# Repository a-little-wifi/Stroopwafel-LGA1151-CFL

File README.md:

# Stroopwafel LGA1151 Intel Coffee Lake motherboard

Trying to see how far I can get with implementing a modern-ish Intel platform in KiCad using public documentation and leaked schematics.

Here's some work in progress pictures (random layout (or ATX standard successor??? 👀)):

Inspired by LCSC carrying LGA1151 sockets: https://www.lcsc.com/product-detail/C2761532.html (thanks for the footprint)

Thanks @mothenjoyer69 for extracting the PCH footprint from a random laptop boardview (LA-F711P)

CPU and PCH schematic symbols fully copied (and partially corrected) from pdf schematics by hand (took like 3 days...)

It's called Stroopwafel because I was eating a stroopwafel when I was trying to come up with a name. Also stroopwafels are supposed to go with coffee and it's Coffee Lake... get it?....

Mostly using LCFC NM-B551 (Lenovo Tiny5) and Wistron 17557-1 Copperbox (Acer N4660G my beloved) schematics for reference atm

The PCH footprint and symbol in this project should be applicable to (most of) Intel's 300 and 400 series chipsets. 300 series goes with 8th/9th gen and 400 series goes with 10th/11th gen.  
I'll be using a 300-series chipset for this project (probably Z390), since I'm using LGA1151. For 400 series you need LGA1200.

The goal is to create an easy to understand board and schematic layout that breaks out as much of the platform capabilities as possible.

Might build a laptop with a desktop CPU for fun later.

Am I insane? maybe. But I don't really see why I shouldn't try at the moment. It's a fun experiment at least.

No idea what board layout I'll use yet, but I don't feel like using a standard ATX formfactor, there's already plenty of boards like that. I kinda wanna make the PCH and CPU sections modular but I'll have to see about the practicalities of that.

I don't know how I'm gonna handle the EC and firmware yet, probably just gonna yoink it from an existing board and pray that it works without too much modification. I'm open to help regarding this. Maybe coreboot/libreboot?

Routing DDR4 will be fun.

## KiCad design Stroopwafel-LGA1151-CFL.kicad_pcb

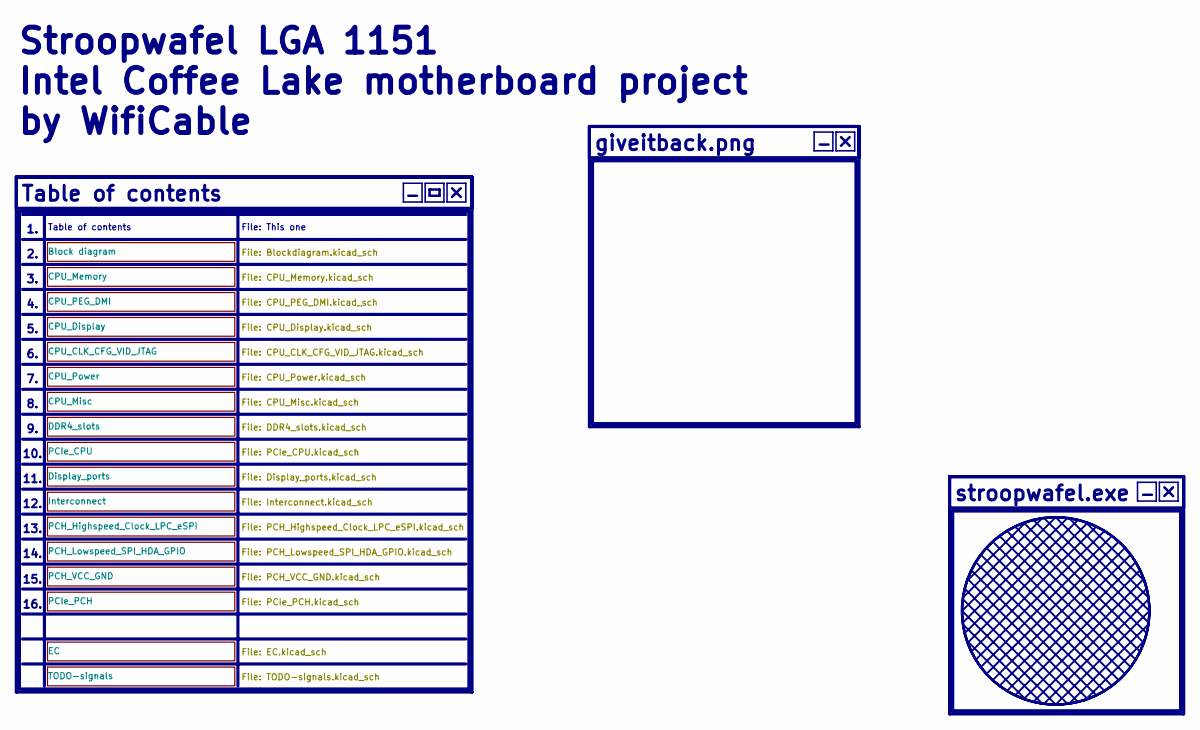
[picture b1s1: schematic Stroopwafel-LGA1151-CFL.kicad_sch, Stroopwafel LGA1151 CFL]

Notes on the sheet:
Stroopwafel LGA 1151 Intel Coffee Lake motherboard project by WifiCable
Table of contents
stroopwafel.exe
11.
15.
File: This one
giveitback.png
14.
16.
13.
10.
12.

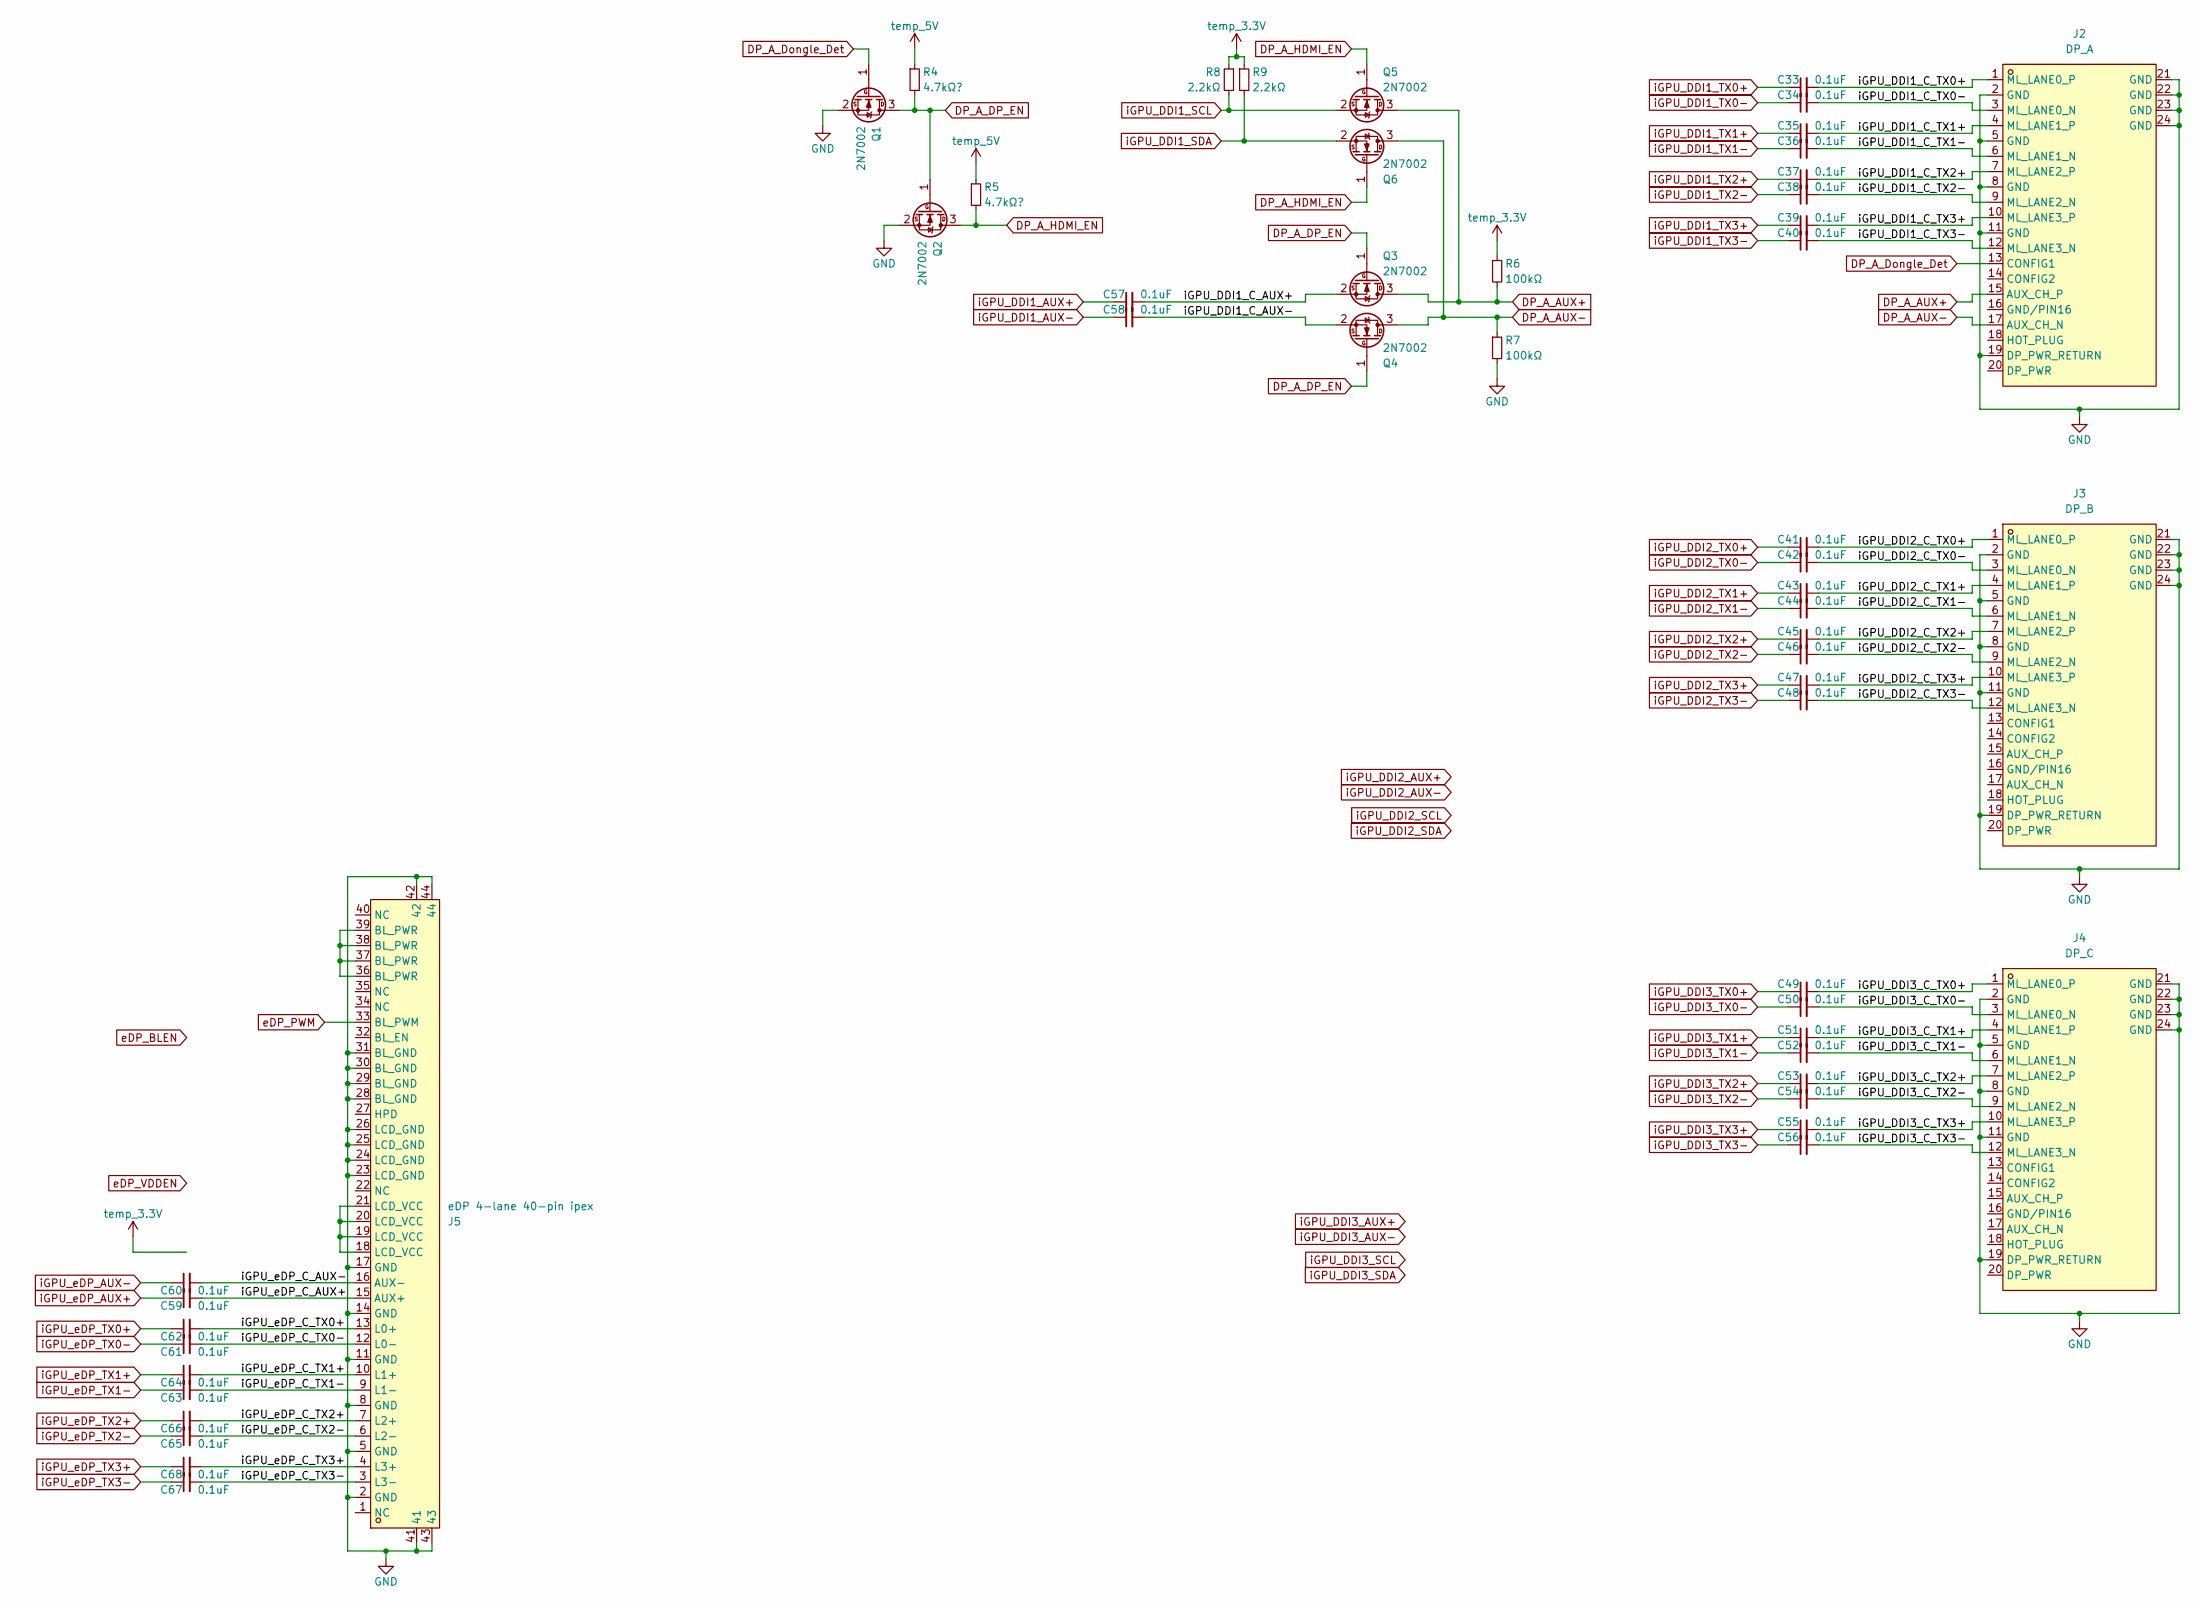
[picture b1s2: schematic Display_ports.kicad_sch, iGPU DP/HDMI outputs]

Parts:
C33, C34, C35, C36, C37, C38, C39, C40, C41, C42, C43, C44, C45, C46, C47, C48, C49, C50, C51, C52, C53, C54, C55, C56, C57, C58, C59, C60, C61, C62, C63, C64, C65, C66, C67, C68: 0.1uF; C_0402_1005Metric
J2: DP_A; DP-SMD_HYC16-DP20-178; LCSC Part C711350
J3: DP_B; DP-SMD_HYC16-DP20-178; LCSC Part C711350
J4: DP_C; DP-SMD_HYC16-DP20-178; LCSC Part C711350
J5: eDP 4-lane 40-pin ipex; 40pIPEX_20455-040E-76
Q1, Q2, Q3, Q4, Q5, Q6: 2N7002; SOT-23
R4, R5: 4.7kΩ?; R_0402_1005Metric
R6, R7: 100kΩ; R_0402_1005Metric
R8, R9: 2.2kΩ; R_0402_1005Metric

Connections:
/Display_ports/iGPU_DDI1_C_AUX+: C57.2, Q3.2 (S)
/Display_ports/iGPU_DDI1_C_AUX-: C58.2, Q4.2 (S)
/Display_ports/iGPU_DDI1_C_TX0+: C33.2, J2.1 (ML_LANE0_P)
/Display_ports/iGPU_DDI1_C_TX0-: C34.2, J2.3 (ML_LANE0_N)
/Display_ports/iGPU_DDI1_C_TX1+: C35.2, J2.4 (ML_LANE1_P)
/Display_ports/iGPU_DDI1_C_TX1-: C36.2, J2.6 (ML_LANE1_N)
/Display_ports/iGPU_DDI1_C_TX2+: C37.2, J2.7 (ML_LANE2_P)
/Display_ports/iGPU_DDI1_C_TX2-: C38.2, J2.9 (ML_LANE2_N)
/Display_ports/iGPU_DDI1_C_TX3+: C39.2, J2.10 (ML_LANE3_P)
/Display_ports/iGPU_DDI1_C_TX3-: C40.2, J2.12 (ML_LANE3_N)
/Display_ports/iGPU_DDI2_C_TX0+: C41.2, J3.1 (ML_LANE0_P)
/Display_ports/iGPU_DDI2_C_TX0-: C42.2, J3.3 (ML_LANE0_N)
/Display_ports/iGPU_DDI2_C_TX1+: C43.2, J3.4 (ML_LANE1_P)
/Display_ports/iGPU_DDI2_C_TX1-: C44.2, J3.6 (ML_LANE1_N)
/Display_ports/iGPU_DDI2_C_TX2+: C45.2, J3.7 (ML_LANE2_P)
/Display_ports/iGPU_DDI2_C_TX2-: C46.2, J3.9 (ML_LANE2_N)
/Display_ports/iGPU_DDI2_C_TX3+: C47.2, J3.10 (ML_LANE3_P)
/Display_ports/iGPU_DDI2_C_TX3-: C48.2, J3.12 (ML_LANE3_N)
/Display_ports/iGPU_DDI3_C_TX0+: C49.2, J4.1 (ML_LANE0_P)
/Display_ports/iGPU_DDI3_C_TX0-: C50.2, J4.3 (ML_LANE0_N)
/Display_ports/iGPU_DDI3_C_TX1+: C51.2, J4.4 (ML_LANE1_P)
/Display_ports/iGPU_DDI3_C_TX1-: C52.2, J4.6 (ML_LANE1_N)
/Display_ports/iGPU_DDI3_C_TX2+: C53.2, J4.7 (ML_LANE2_P)
/Display_ports/iGPU_DDI3_C_TX2-: C54.2, J4.9 (ML_LANE2_N)
/Display_ports/iGPU_DDI3_C_TX3+: C55.2, J4.10 (ML_LANE3_P)
/Display_ports/iGPU_DDI3_C_TX3-: C56.2, J4.12 (ML_LANE3_N)
/Display_ports/iGPU_eDP_C_AUX+: C59.2, J5.15 (AUX+)
/Display_ports/iGPU_eDP_C_AUX-: C60.2, J5.16 (AUX-)
/Display_ports/iGPU_eDP_C_TX0+: C62.2, J5.13 (L0+)
/Display_ports/iGPU_eDP_C_TX0-: C61.2, J5.12 (L0-)
/Display_ports/iGPU_eDP_C_TX1+: C64.2, J5.10 (L1+)
/Display_ports/iGPU_eDP_C_TX1-: C63.2, J5.9 (L1-)
/Display_ports/iGPU_eDP_C_TX2+: C66.2, J5.7 (L2+)
/Display_ports/iGPU_eDP_C_TX2-: C65.2, J5.6 (L2-)
/Display_ports/iGPU_eDP_C_TX3+: C68.2, J5.4 (L3+)
/Display_ports/iGPU_eDP_C_TX3-: C67.2, J5.3 (L3-)
DP_A_AUX+: J2.15 (AUX_CH_P), Q3.3 (D), Q5.3 (D), R6.2
DP_A_AUX-: J2.17 (AUX_CH_N), Q4.3 (D), Q6.3 (D), R7.1
DP_A_DP_EN: Q1.3 (D), Q2.1 (G), Q3.1 (G), Q4.1 (G), R4.2
DP_A_Dongle_Det: J2.13 (CONFIG1), Q1.1 (G)
DP_A_HDMI_EN: Q2.3 (D), Q5.1 (G), Q6.1 (G), R5.2
GND: J2.2 (GND), J2.5 (GND), J2.8 (GND), J2.11 (GND), J2.19 (DP_PWR_RETURN), J2.21 (GND), J2.22 (GND), J2.23 (GND), J2.24 (GND), J3.2 (GND), J3.5 (GND), J3.8 (GND), J3.11 (GND), J3.19 (DP_PWR_RETURN), J3.21 (GND), J3.22 (GND), J3.23 (GND), J3.24 (GND), J4.2 (GND), J4.5 (GND), J4.8 (GND), J4.11 (GND), J4.19 (DP_PWR_RETURN), J4.21 (GND), J4.22 (GND), J4.23 (GND), J4.24 (GND), J5.2 (GND), J5.5 (GND), J5.8 (GND), J5.11 (GND), J5.14 (GND), J5.17 (GND), J5.23 (LCD_GND), J5.24 (LCD_GND), J5.25 (LCD_GND), J5.26 (LCD_GND), J5.28 (BL_GND), J5.29 (BL_GND), J5.30 (BL_GND), J5.31 (BL_GND), J5.41, J5.42, J5.43, J5.44, Q1.2 (S), Q2.2 (S), R7.2; also elsewhere on the board
unnamed: J5.36 (BL_PWR), J5.37 (BL_PWR), J5.38 (BL_PWR), J5.39 (BL_PWR)
unnamed: J5.18 (LCD_VCC), J5.19 (LCD_VCC), J5.20 (LCD_VCC), J5.21 (LCD_VCC)
eDP_PWM: J5.33 (BL_PWM); also elsewhere on the board
iGPU_DDI1_AUX+: C57.1; also elsewhere on the board
iGPU_DDI1_AUX-: C58.1; also elsewhere on the board
iGPU_DDI1_SCL: Q5.2 (S), R8.2; also elsewhere on the board
iGPU_DDI1_SDA: Q6.2 (S), R9.2; also elsewhere on the board
iGPU_DDI1_TX0+: C33.1; also elsewhere on the board
iGPU_DDI1_TX0-: C34.1; also elsewhere on the board
iGPU_DDI1_TX1+: C35.1; also elsewhere on the board
iGPU_DDI1_TX1-: C36.1; also elsewhere on the board
iGPU_DDI1_TX2+: C37.1; also elsewhere on the board
iGPU_DDI1_TX2-: C38.1; also elsewhere on the board
iGPU_DDI1_TX3+: C39.1; also elsewhere on the board
iGPU_DDI1_TX3-: C40.1; also elsewhere on the board
iGPU_DDI2_TX0+: C41.1; also elsewhere on the board
iGPU_DDI2_TX0-: C42.1; also elsewhere on the board
iGPU_DDI2_TX1+: C43.1; also elsewhere on the board
iGPU_DDI2_TX1-: C44.1; also elsewhere on the board
iGPU_DDI2_TX2+: C45.1; also elsewhere on the board
iGPU_DDI2_TX2-: C46.1; also elsewhere on the board
iGPU_DDI2_TX3+: C47.1; also elsewhere on the board
iGPU_DDI2_TX3-: C48.1; also elsewhere on the board
iGPU_DDI3_TX0+: C49.1; also elsewhere on the board
iGPU_DDI3_TX0-: C50.1; also elsewhere on the board
iGPU_DDI3_TX1+: C51.1; also elsewhere on the board
iGPU_DDI3_TX1-: C52.1; also elsewhere on the board
iGPU_DDI3_TX2+: C53.1; also elsewhere on the board
iGPU_DDI3_TX2-: C54.1; also elsewhere on the board
iGPU_DDI3_TX3+: C55.1; also elsewhere on the board
iGPU_DDI3_TX3-: C56.1; also elsewhere on the board
iGPU_eDP_AUX+: C59.1; also elsewhere on the board
iGPU_eDP_AUX-: C60.1; also elsewhere on the board
iGPU_eDP_TX0+: C62.1; also elsewhere on the board
iGPU_eDP_TX0-: C61.1; also elsewhere on the board
iGPU_eDP_TX1+: C64.1; also elsewhere on the board
iGPU_eDP_TX1-: C63.1; also elsewhere on the board
iGPU_eDP_TX2+: C66.1; also elsewhere on the board
iGPU_eDP_TX2-: C65.1; also elsewhere on the board
iGPU_eDP_TX3+: C68.1; also elsewhere on the board
iGPU_eDP_TX3-: C67.1; also elsewhere on the board
temp_3.3V: R6.1, R8.1, R9.1; also elsewhere on the board
temp_5V: R4.1, R5.1

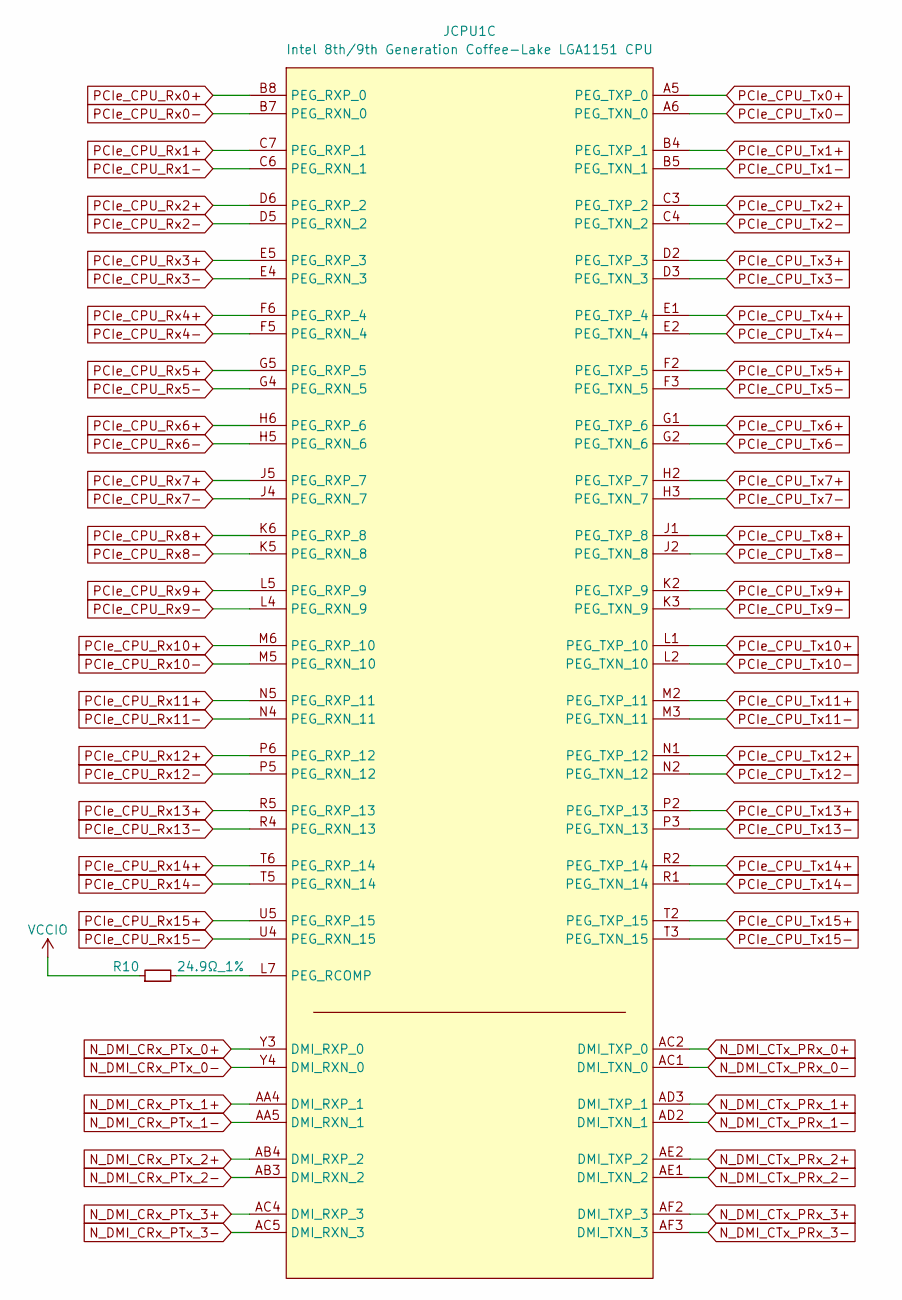
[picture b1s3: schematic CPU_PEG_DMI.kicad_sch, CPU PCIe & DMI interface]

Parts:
JCPU1: Intel 8th/9th Generation Coffee-Lake LGA1151 CPU; LGA-1151_L47.1-W42.5-P0.91_PE115127-4041-01H
R10: 24.9Ω_1%; R_0402_1005Metric

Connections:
N_DMI_CRx_PTx_0+: JCPU1.Y3 (DMI_RXP_0); also elsewhere on the board
N_DMI_CRx_PTx_0-: JCPU1.Y4 (DMI_RXN_0); also elsewhere on the board
N_DMI_CRx_PTx_1+: JCPU1.AA4 (DMI_RXP_1); also elsewhere on the board
N_DMI_CRx_PTx_1-: JCPU1.AA5 (DMI_RXN_1); also elsewhere on the board
N_DMI_CRx_PTx_2+: JCPU1.AB4 (DMI_RXP_2); also elsewhere on the board
N_DMI_CRx_PTx_2-: JCPU1.AB3 (DMI_RXN_2); also elsewhere on the board
N_DMI_CRx_PTx_3+: JCPU1.AC4 (DMI_RXP_3); also elsewhere on the board
N_DMI_CRx_PTx_3-: JCPU1.AC5 (DMI_RXN_3); also elsewhere on the board
N_DMI_CTx_PRx_0+: JCPU1.AC2 (DMI_TXP_0); also elsewhere on the board
N_DMI_CTx_PRx_0-: JCPU1.AC1 (DMI_TXN_0); also elsewhere on the board
N_DMI_CTx_PRx_1+: JCPU1.AD3 (DMI_TXP_1); also elsewhere on the board
N_DMI_CTx_PRx_1-: JCPU1.AD2 (DMI_TXN_1); also elsewhere on the board
N_DMI_CTx_PRx_2+: JCPU1.AE2 (DMI_TXP_2); also elsewhere on the board
N_DMI_CTx_PRx_2-: JCPU1.AE1 (DMI_TXN_2); also elsewhere on the board
N_DMI_CTx_PRx_3+: JCPU1.AF2 (DMI_TXP_3); also elsewhere on the board
N_DMI_CTx_PRx_3-: JCPU1.AF3 (DMI_TXN_3); also elsewhere on the board
unnamed: JCPU1.L7 (PEG_RCOMP), R10.2
PCIe_CPU_Rx0+: JCPU1.B8 (PEG_RXP_0); also elsewhere on the board
PCIe_CPU_Rx0-: JCPU1.B7 (PEG_RXN_0); also elsewhere on the board
PCIe_CPU_Rx1+: JCPU1.C7 (PEG_RXP_1); also elsewhere on the board
PCIe_CPU_Rx1-: JCPU1.C6 (PEG_RXN_1); also elsewhere on the board
PCIe_CPU_Rx2+: JCPU1.D6 (PEG_RXP_2); also elsewhere on the board
PCIe_CPU_Rx2-: JCPU1.D5 (PEG_RXN_2); also elsewhere on the board
PCIe_CPU_Rx3+: JCPU1.E5 (PEG_RXP_3); also elsewhere on the board
PCIe_CPU_Rx3-: JCPU1.E4 (PEG_RXN_3); also elsewhere on the board
PCIe_CPU_Rx4+: JCPU1.F6 (PEG_RXP_4); also elsewhere on the board
PCIe_CPU_Rx4-: JCPU1.F5 (PEG_RXN_4); also elsewhere on the board
PCIe_CPU_Rx5+: JCPU1.G5 (PEG_RXP_5); also elsewhere on the board
PCIe_CPU_Rx5-: JCPU1.G4 (PEG_RXN_5); also elsewhere on the board
PCIe_CPU_Rx6+: JCPU1.H6 (PEG_RXP_6); also elsewhere on the board
PCIe_CPU_Rx6-: JCPU1.H5 (PEG_RXN_6); also elsewhere on the board
PCIe_CPU_Rx7+: JCPU1.J5 (PEG_RXP_7); also elsewhere on the board
PCIe_CPU_Rx7-: JCPU1.J4 (PEG_RXN_7); also elsewhere on the board
PCIe_CPU_Rx8+: JCPU1.K6 (PEG_RXP_8); also elsewhere on the board
PCIe_CPU_Rx8-: JCPU1.K5 (PEG_RXN_8); also elsewhere on the board
PCIe_CPU_Rx9+: JCPU1.L5 (PEG_RXP_9); also elsewhere on the board
PCIe_CPU_Rx9-: JCPU1.L4 (PEG_RXN_9); also elsewhere on the board
PCIe_CPU_Rx10+: JCPU1.M6 (PEG_RXP_10); also elsewhere on the board
PCIe_CPU_Rx10-: JCPU1.M5 (PEG_RXN_10); also elsewhere on the board
PCIe_CPU_Rx11+: JCPU1.N5 (PEG_RXP_11); also elsewhere on the board
PCIe_CPU_Rx11-: JCPU1.N4 (PEG_RXN_11); also elsewhere on the board
PCIe_CPU_Rx12+: JCPU1.P6 (PEG_RXP_12); also elsewhere on the board
PCIe_CPU_Rx12-: JCPU1.P5 (PEG_RXN_12); also elsewhere on the board
PCIe_CPU_Rx13+: JCPU1.R5 (PEG_RXP_13); also elsewhere on the board
PCIe_CPU_Rx13-: JCPU1.R4 (PEG_RXN_13); also elsewhere on the board
PCIe_CPU_Rx14+: JCPU1.T6 (PEG_RXP_14); also elsewhere on the board
PCIe_CPU_Rx14-: JCPU1.T5 (PEG_RXN_14); also elsewhere on the board
PCIe_CPU_Rx15+: JCPU1.U5 (PEG_RXP_15); also elsewhere on the board
PCIe_CPU_Rx15-: JCPU1.U4 (PEG_RXN_15); also elsewhere on the board
PCIe_CPU_Tx0+: JCPU1.A5 (PEG_TXP_0); also elsewhere on the board
PCIe_CPU_Tx0-: JCPU1.A6 (PEG_TXN_0); also elsewhere on the board
PCIe_CPU_Tx1+: JCPU1.B4 (PEG_TXP_1); also elsewhere on the board
PCIe_CPU_Tx1-: JCPU1.B5 (PEG_TXN_1); also elsewhere on the board
PCIe_CPU_Tx2+: JCPU1.C3 (PEG_TXP_2); also elsewhere on the board
PCIe_CPU_Tx2-: JCPU1.C4 (PEG_TXN_2); also elsewhere on the board
PCIe_CPU_Tx3+: JCPU1.D2 (PEG_TXP_3); also elsewhere on the board
PCIe_CPU_Tx3-: JCPU1.D3 (PEG_TXN_3); also elsewhere on the board
PCIe_CPU_Tx4+: JCPU1.E1 (PEG_TXP_4); also elsewhere on the board
PCIe_CPU_Tx4-: JCPU1.E2 (PEG_TXN_4); also elsewhere on the board
PCIe_CPU_Tx5+: JCPU1.F2 (PEG_TXP_5); also elsewhere on the board
PCIe_CPU_Tx5-: JCPU1.F3 (PEG_TXN_5); also elsewhere on the board
PCIe_CPU_Tx6+: JCPU1.G1 (PEG_TXP_6); also elsewhere on the board
PCIe_CPU_Tx6-: JCPU1.G2 (PEG_TXN_6); also elsewhere on the board
PCIe_CPU_Tx7+: JCPU1.H2 (PEG_TXP_7); also elsewhere on the board
PCIe_CPU_Tx7-: JCPU1.H3 (PEG_TXN_7); also elsewhere on the board
PCIe_CPU_Tx8+: JCPU1.J1 (PEG_TXP_8); also elsewhere on the board
PCIe_CPU_Tx8-: JCPU1.J2 (PEG_TXN_8); also elsewhere on the board
PCIe_CPU_Tx9+: JCPU1.K2 (PEG_TXP_9); also elsewhere on the board
PCIe_CPU_Tx9-: JCPU1.K3 (PEG_TXN_9); also elsewhere on the board
PCIe_CPU_Tx10+: JCPU1.L1 (PEG_TXP_10); also elsewhere on the board
PCIe_CPU_Tx10-: JCPU1.L2 (PEG_TXN_10); also elsewhere on the board
PCIe_CPU_Tx11+: JCPU1.M2 (PEG_TXP_11); also elsewhere on the board
PCIe_CPU_Tx11-: JCPU1.M3 (PEG_TXN_11); also elsewhere on the board
PCIe_CPU_Tx12+: JCPU1.N1 (PEG_TXP_12); also elsewhere on the board
PCIe_CPU_Tx12-: JCPU1.N2 (PEG_TXN_12); also elsewhere on the board
PCIe_CPU_Tx13+: JCPU1.P2 (PEG_TXP_13); also elsewhere on the board
PCIe_CPU_Tx13-: JCPU1.P3 (PEG_TXN_13); also elsewhere on the board
PCIe_CPU_Tx14+: JCPU1.R2 (PEG_TXP_14); also elsewhere on the board
PCIe_CPU_Tx14-: JCPU1.R1 (PEG_TXN_14); also elsewhere on the board
PCIe_CPU_Tx15+: JCPU1.T2 (PEG_TXP_15); also elsewhere on the board
PCIe_CPU_Tx15-: JCPU1.T3 (PEG_TXN_15); also elsewhere on the board
VCCIO: R10.1; also elsewhere on the board

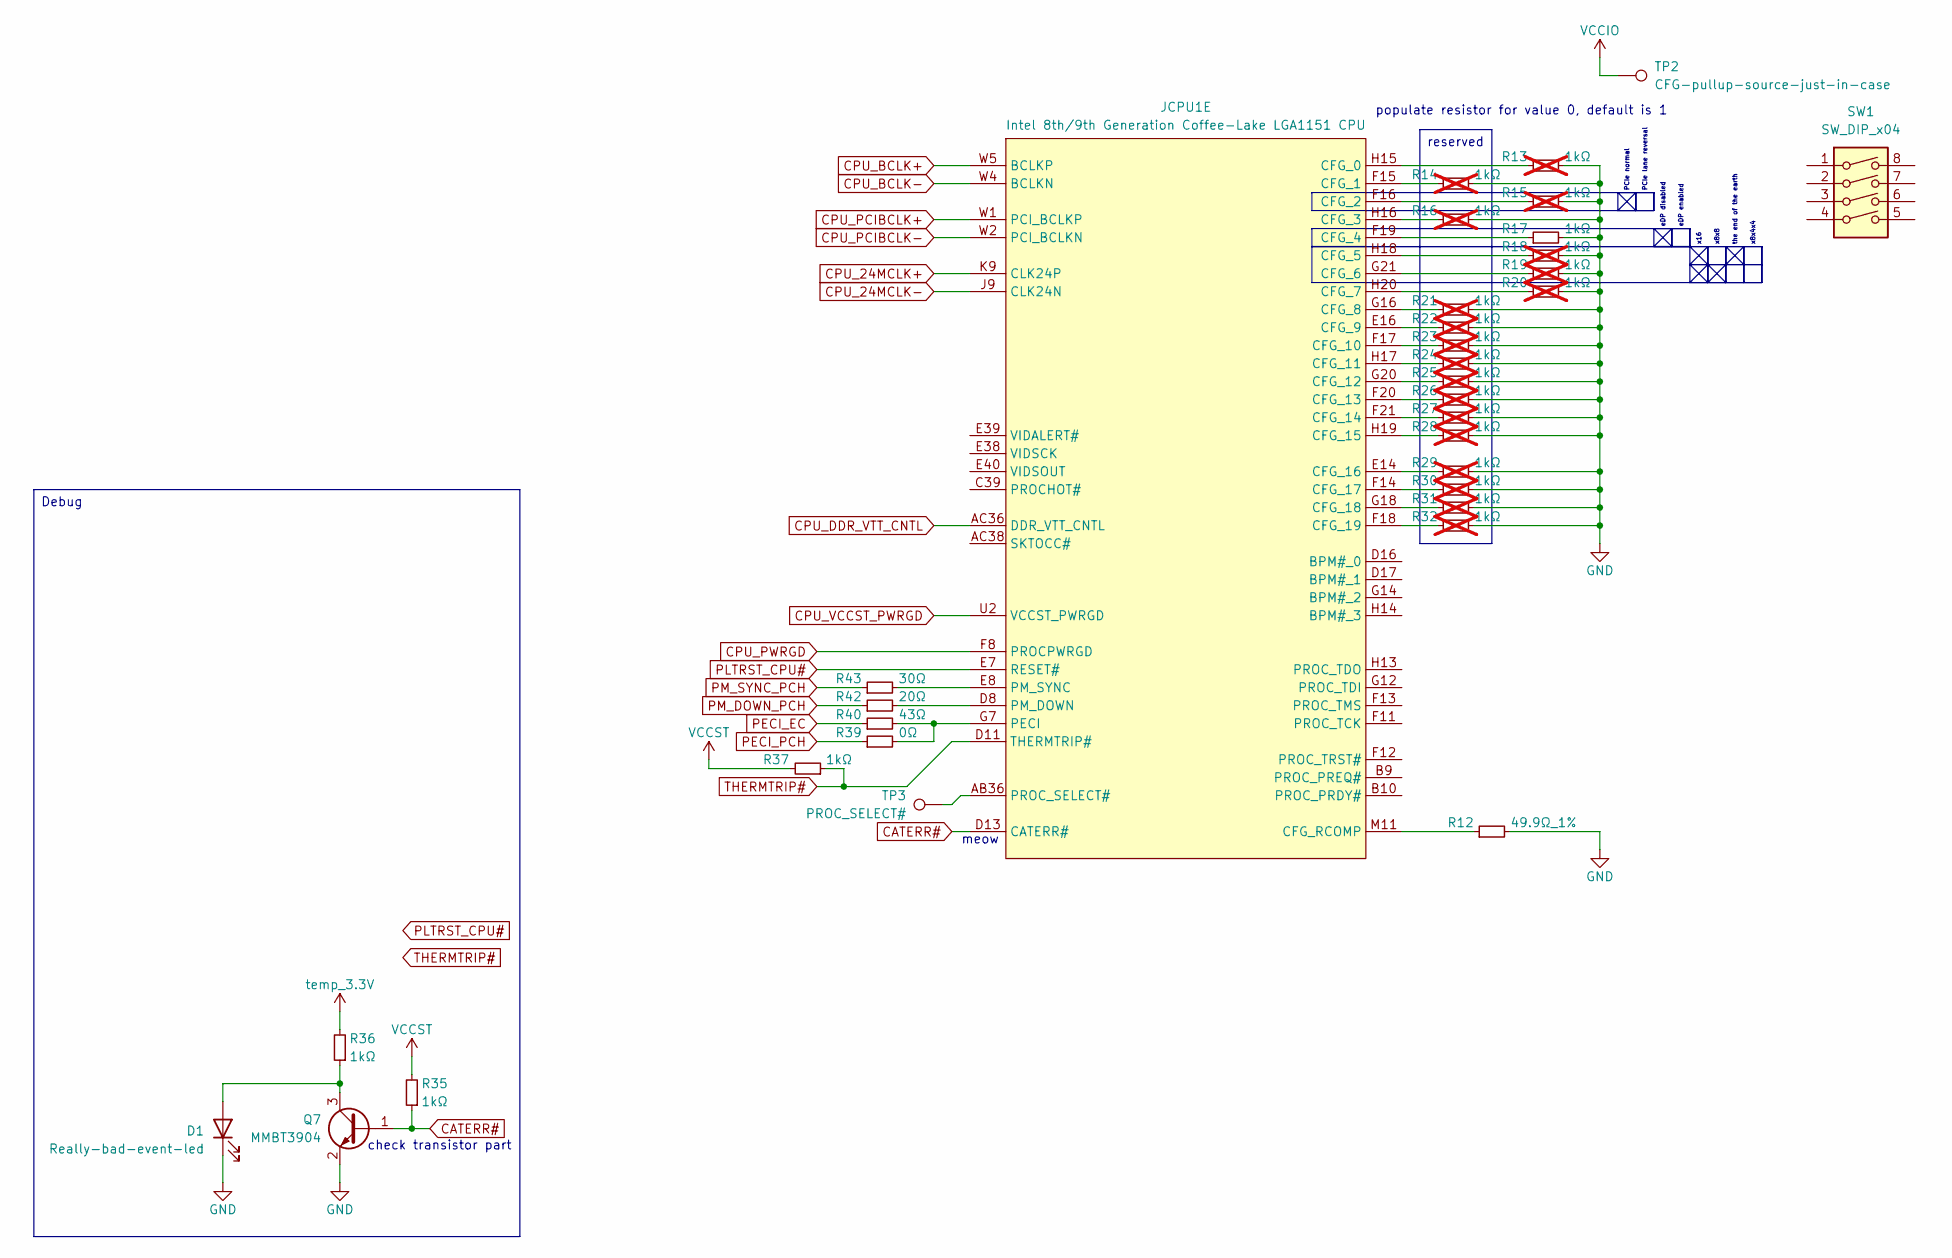
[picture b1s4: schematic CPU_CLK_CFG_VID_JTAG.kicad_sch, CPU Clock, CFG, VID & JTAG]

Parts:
D1: Really-bad-event-led; LED_0603_1608Metric
JCPU1: Intel 8th/9th Generation Coffee-Lake LGA1151 CPU; LGA-1151_L47.1-W42.5-P0.91_PE115127-4041-01H
Q7: MMBT3904; SOT-23
R12: 49.9Ω_1%; R_0402_1005Metric
R13, R14, R15, R16, R18, R19, R20, R21, R22, R23, R24, R25, R26, R27, R28, R29, R30, R31, R32: 1kΩ; R_0402_1005Metric; not fitted
R17, R35, R36, R37: 1kΩ; R_0402_1005Metric
R39: 0Ω; R_0402_1005Metric
R40: 43Ω; R_0402_1005Metric
R42: 20Ω; R_0402_1005Metric
R43: 30Ω; R_0402_1005Metric
SW1: SW_DIP_x04
TP2: CFG-pullup-source-just-in-case; TestPoint_Pad_D2.0mm
TP3: PROC_SELECT#; TestPoint_Pad_D2.0mm

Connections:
CATERR#: JCPU1.D13 (CATERR#), Q7.1 (B), R35.1
CPU_24MCLK+: JCPU1.K9 (CLK24P); also elsewhere on the board
CPU_24MCLK-: JCPU1.J9 (CLK24N); also elsewhere on the board
CPU_BCLK+: JCPU1.W5 (BCLKP); also elsewhere on the board
CPU_BCLK-: JCPU1.W4 (BCLKN); also elsewhere on the board
CPU_DDR_VTT_CNTL: JCPU1.AC36 (DDR_VTT_CNTL)
CPU_PCIBCLK+: JCPU1.W1 (PCI_BCLKP); also elsewhere on the board
CPU_PCIBCLK-: JCPU1.W2 (PCI_BCLKN); also elsewhere on the board
CPU_PWRGD: JCPU1.F8 (PROCPWRGD); also elsewhere on the board
CPU_VCCST_PWRGD: JCPU1.U2 (VCCST_PWRGD)
GND: D1.1 (K), Q7.2 (E), R12.2, R13.2, R14.2, R15.2, R16.2, R17.2, R18.2, R19.2, R20.2, R21.2, R22.2, R23.2, R24.2, R25.2, R26.2, R27.2, R28.2, R29.2, R30.2, R31.2, R32.2; also elsewhere on the board
unnamed: D1.2 (A), Q7.3 (C), R36.1
unnamed: JCPU1.H15 (CFG_0), R13.1
unnamed: JCPU1.F15 (CFG_1), R14.1
unnamed: JCPU1.F16 (CFG_2), R15.1
unnamed: JCPU1.H16 (CFG_3), R16.1
unnamed: JCPU1.F19 (CFG_4), R17.1
unnamed: JCPU1.H18 (CFG_5), R18.1
unnamed: JCPU1.G21 (CFG_6), R19.1
unnamed: JCPU1.H20 (CFG_7), R20.1
unnamed: JCPU1.G16 (CFG_8), R21.1
unnamed: JCPU1.E16 (CFG_9), R22.1
unnamed: JCPU1.F17 (CFG_10), R23.1
unnamed: JCPU1.H17 (CFG_11), R24.1
unnamed: JCPU1.G20 (CFG_12), R25.1
unnamed: JCPU1.F20 (CFG_13), R26.1
unnamed: JCPU1.F21 (CFG_14), R27.1
unnamed: JCPU1.H19 (CFG_15), R28.1
unnamed: JCPU1.E14 (CFG_16), R29.1
unnamed: JCPU1.F14 (CFG_17), R30.1
unnamed: JCPU1.G18 (CFG_18), R31.1
unnamed: JCPU1.F18 (CFG_19), R32.1
unnamed: JCPU1.M11 (CFG_RCOMP), R12.1
unnamed: JCPU1.G7 (PECI), R39.2, R40.2
unnamed: JCPU1.D8 (PM_DOWN), R42.2
unnamed: JCPU1.E8 (PM_SYNC), R43.2
unnamed: JCPU1.AB36 (PROC_SELECT#), TP3.1
PECI_EC: R40.1
PECI_PCH: R39.1; also elsewhere on the board
PLTRST_CPU#: JCPU1.E7 (RESET#); also elsewhere on the board
PM_DOWN_PCH: R42.1; also elsewhere on the board
PM_SYNC_PCH: R43.1; also elsewhere on the board
THERMTRIP#: JCPU1.D11 (THERMTRIP#), R37.1; also elsewhere on the board
VCCIO: TP2.1; also elsewhere on the board
VCCST: R35.2, R37.2; also elsewhere on the board
temp_3.3V: R36.2; also elsewhere on the board

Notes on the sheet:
PCIe lane reversal
eDP disabled
x8x4x4
x16
x8x8
check transistor part
eDP enabled
PCIe normal
the end of the earth
meow
populate resistor for value 0, default is 1
reserved
Debug

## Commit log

2025-09-05 Added files
2025-09-05 Added work in progress CPU symbol and socket footprint
2025-09-06 Completed DDR4 channel 0 symbol
2025-09-06 added WIP symbol for DDR4 channel 1
2025-09-06 Completed DDR4 channel 1 symbol
2025-09-06 rotated socket
2025-09-06 Added PEG/DMI symbol
2025-09-06 stroopwafel
2025-09-06 Added CPU DDI symbol
2025-09-06 Added CPU clock/cfg/vid/jtag symbol
2025-09-06 Added CPU GND and Core VCC symbols
2025-09-06 Added iGPU VCC symbol
2025-09-06 Added CPU Misc VCC symbol
2025-09-06 Added CPU Misc & RSVD symbol
2025-09-06 Added the last 2 CPU Ground symbols, CPU symbol set complete
2025-09-06 Connected CPU ground
2025-09-06 Added first PCH symbol and footprint
    THANKS @mothenjoyer69 so much for extracting and converting the PCH footprint from a laptop boardview ❤️
2025-09-07 Added all the PCH symbols
    that took 1.5 days straight lol
2025-09-09 Fixed some PCH pin names
2025-09-09 replaced PCH symbol set with modified more sane version
    seriously what was intel thinking when laying out half of those symbols, i can't make sense of their choices
    if you want the original version take it from the commit before this one I guess
2025-09-09 Connected DMI for fun (with lane reversal)
2025-09-09 Moved PCH symbols to their own pages
2025-09-09 Titled PCH pages
2025-09-09 Updated pcb file for new schematic layout
2025-09-09 Fixed some incorrect pin names
    somehow it was wrong on Intel's symbol on the reference schematic, the datasheet has it correct. I wonder how many more pins are like this.....
2025-10-09 Added sodimm memory slots and mostly hooked them up on the schematic
2025-10-09 Added pretty colors
    pretty fun to do
2025-10-09 Added PCIe x16 slot
2025-10-12 Added pcie slot and cpu clocks
2025-10-13 Some DP and power work
2025-10-13 More DP
2025-10-15 Wrote a readme
2025-10-15 Added some more to the readme and added Intel's public datasheets
    hope it's ok to put those in here
2025-10-15 adjusted picture formatting, hope they show up next to each other on github now lol
2025-10-15 ig github doesn't wanna show them next to each other. like this then
2025-10-15 Added note about Intel schematic symbol corrections
    Seriously who made those, awful layout + didn't even fully match the datasheet.
    There might be more to fix, will see as I go.
2025-10-15 Added PCH SKU IO table screenshot from datasheet to schematic
    and a note about display audio
2025-10-18 Added DP_A DP++ HDMI dongle detection circuit
2025-10-18 added DP_A DDC pullups
2025-10-22 partially added eDP + rearranged other display stuff
2025-10-23 Added LGA1151 socket bracket holes
    stolen from another lga1151 footprint that has wrong pin numbers....
2025-10-24 Added CPU CFG resistors
2025-10-26 Added PCH PCIe rootport/bifurcation notes
2025-10-26 Fixed 2 pins that somehow disappeared from schematic
    i blame my kicad libraries being weird lol
2025-10-28 Made a cool table of contents on the root schematic page
2025-10-28 moved root page stuff around a bit
2025-10-28 stroopwafel.exe
2025-10-28 Fixed entire schematic being broken
    somehow every symbol with index 1 broke and updating the pcb stopped working. how does that even happen. oh well it's fixed now
2025-11-03 nooo they be stealin my stroopwafel
2025-11-13 implemented some misc cpu signals
2026-01-03 idek what i changed anymore but there's a bunch of new stuff lol
    iirc i did some more misc cpu pins and a bunch of pch pcie stuff
2026-01-04 more pcie notes
2026-03-17 Restructured schematic
2026-05-30 Added interconnect between CPU and PCH boards and added ATX board outline
2026-05-31 Added more PCIe slots and mounting holes
